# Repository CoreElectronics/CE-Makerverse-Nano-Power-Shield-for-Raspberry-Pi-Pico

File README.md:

# Makerverse™ Nano Power Timer HAT for Raspberry Pi Pico

This is the repo for the Core Electronics [Makerverse Nano Power Timer HAT for Raspberry Pi Pico](https://core-electronics.com.au/catalog/product/view/sku/ce08492).

The PCB layout project requires KiCAD 6.0 or newer to view. The schematic is provided in PDF format in the Documents folder.

## License
This project is open source - please review the LICENSE.md file for further licensing information.

If you have any technical questions, or concerns about licensing, please contact technical support on the [Core Electronics forums](https://forum.core-electronics.com.au/).

*\"PiicoDev\" and the PiicoDev logo are trademarks of Core Electronics Pty Ltd.*

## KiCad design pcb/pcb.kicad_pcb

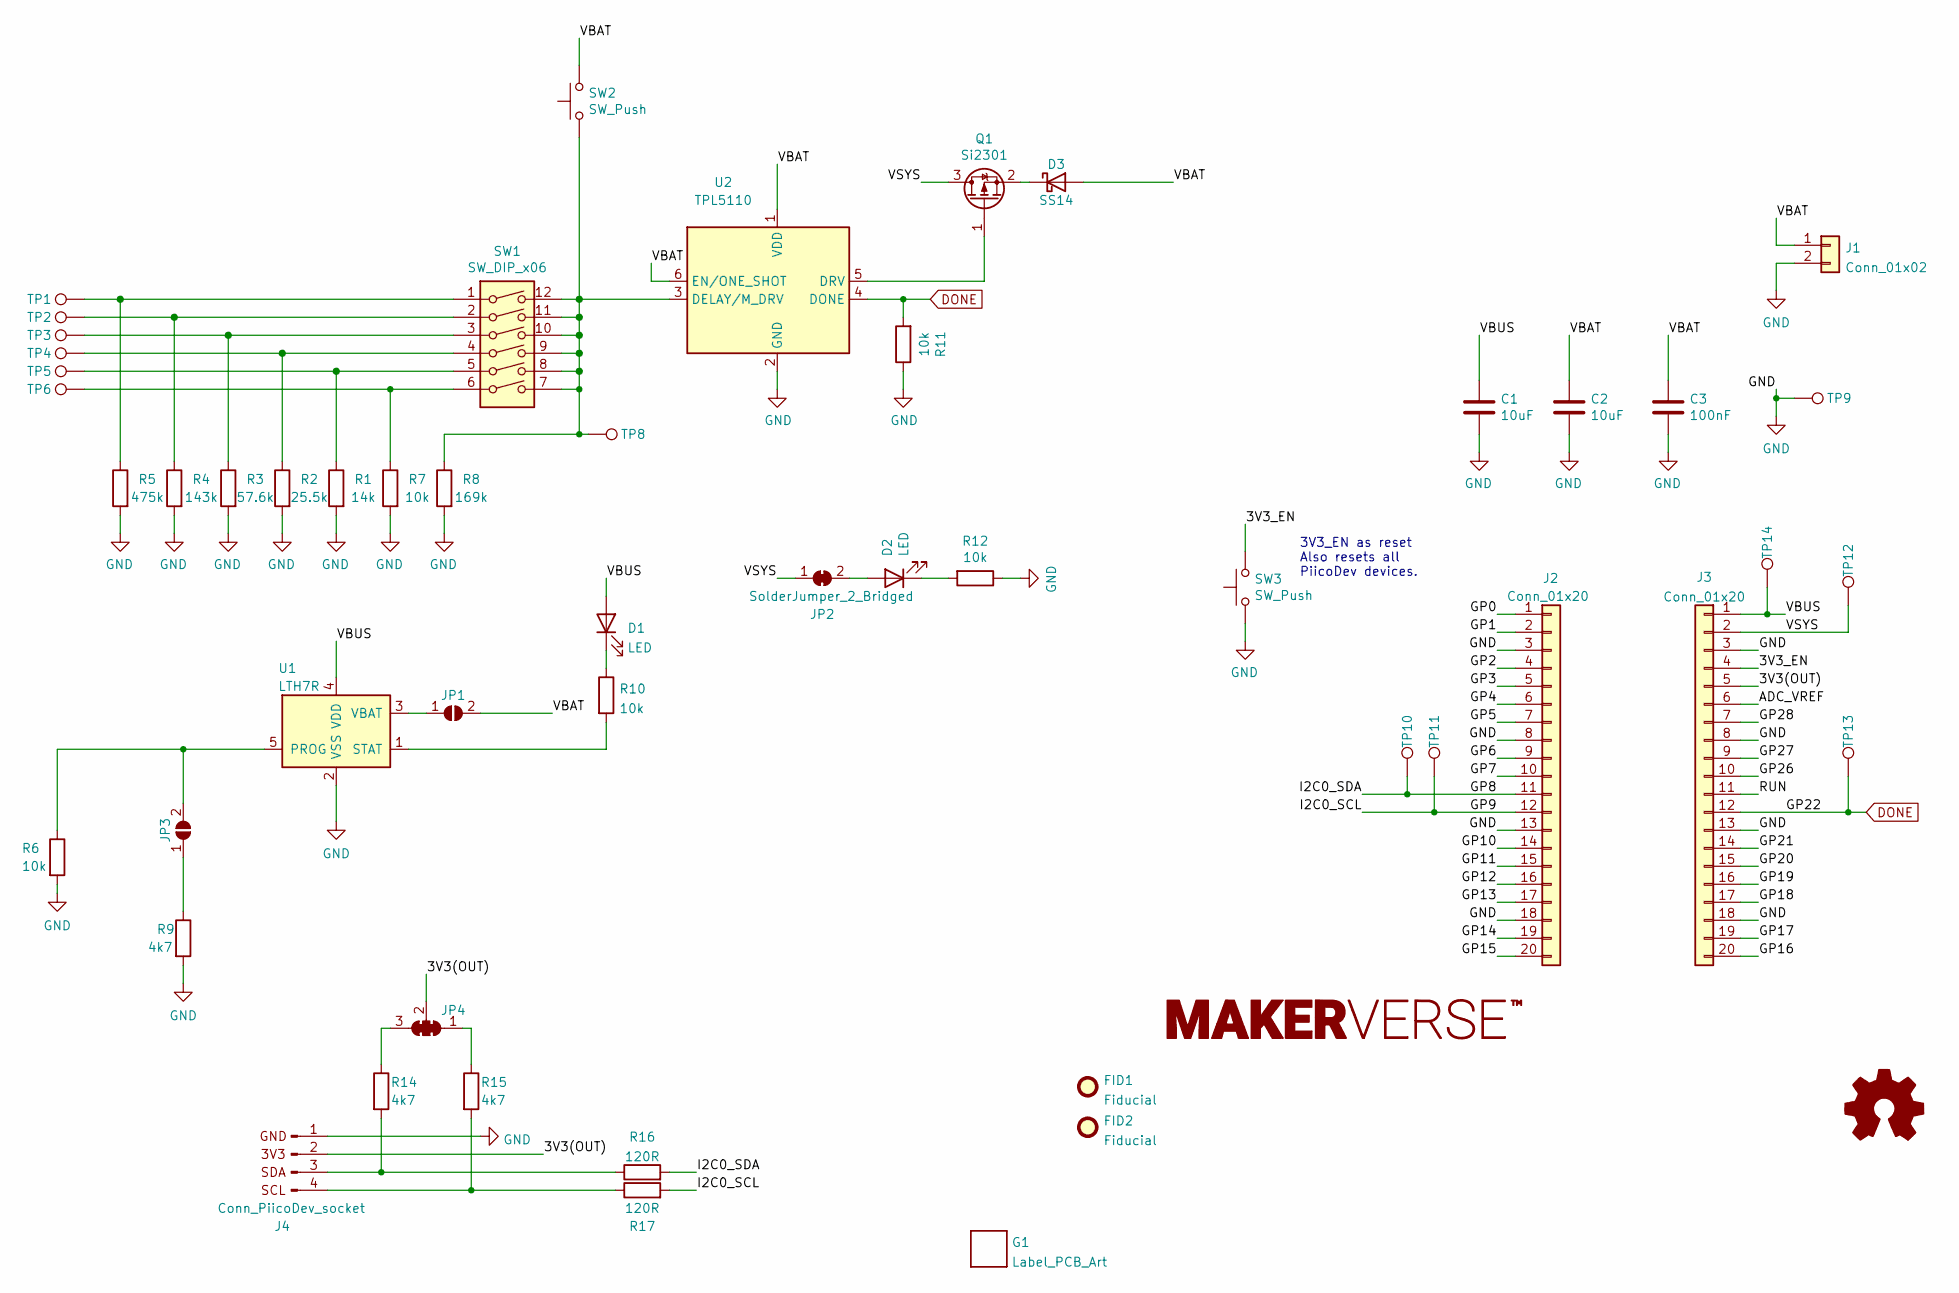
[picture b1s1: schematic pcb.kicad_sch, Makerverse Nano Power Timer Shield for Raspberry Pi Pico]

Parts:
C1, C2: 10uF; C_0603_1608Metric
C3: 100nF; C_0402_1005Metric
D1, D2: LED; LED_0603_1608Metric
D3: SS14; D_SMA
FID1, FID2: Fiducial; Fiducial_1mm_Mask2mm
G1: Label_PCB_Art; CE08492
G2: LOGO_Makerverse; makerverse_logo_short_14.0x2.4mm
J1: Conn_01x02; JST_PH_S2B-PH-SM4-TB_1x02-1MP_P2.00mm_Horizontal
J2, J3: Conn_01x20; PinSocket_1x20_P2.54mm_Vertical-Large-Pads
J4: Conn_PiicoDev_socket; JST_SH_SM04B-SRSS-TB_1x04-1MP_P1.00mm_Horizontal
JP1, JP3: SolderJumper_2_Open; SolderJumper-2_P1.3mm_Open_RoundedPad1.0x1.5mm
JP2: SolderJumper_2_Bridged; SolderJumper-2_P1.3mm_Bridged_RoundedPad1.0x1.5mm
JP4: SolderJumper_3_Bridged123; SolderJumper-3_P1.3mm_Closed_RoundedPad1.0x1.5mm_NumberLabe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
Q1: Si2301; SOT-23
R1: 14k; R_0402_1005Metric
R2: 25.5k; R_0402_1005Metric
R3: 57.6k; R_0402_1005Metric
R4: 143k; R_0402_1005Metric
R5: 475k; R_0402_1005Metric
R6, R7, R10, R11, R12: 10k; R_0402_1005Metric
R8: 169k; R_0402_1005Metric
R9, R14, R15: 4k7; R_0402_1005Metric
R16, R17: 120R; R_0402_1005Metric
SW1: SW_DIP_x06; SW_DIP_SPSTx06_Slide_6.7x16.8mm_W8.61mm_P2.54mm_LowProfile
SW2, SW3: SW_Push; SW_Tactile_5x5
TP1, TP2, TP3, TP4, TP5, TP6, TP8, TP9, TP10, TP11, TP12, TP13, TP14: TestPoint; TestPoint_Pad_D1.5mm
U1: LTH7R; SOT-23-5
U2: TPL5110; SOT-23-6

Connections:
/3V3(OUT): J3.5, J4.2, JP4.2 (C)
/3V3_EN: J3.4, SW3.2
/ADC_VREF: J3.6
/GP0: J2.1
/GP1: J2.2
/GP2: J2.4
/GP3: J2.5
/GP4: J2.6
/GP5: J2.7
/GP6: J2.9
/GP7: J2.10
/GP8: J2.11, R16.2, TP10.1
/GP9: J2.12, R17.2, TP11.1
/GP10: J2.14
/GP11: J2.15
/GP12: J2.16
/GP13: J2.17
/GP14: J2.19
/GP15: J2.20
/GP16: J3.20
/GP17: J3.19
/GP18: J3.17
/GP19: J3.16
/GP20: J3.15
/GP21: J3.14
/GP26: J3.10
/GP27: J3.9
/GP28: J3.7
/RUN: J3.11
/VBAT: C2.1, C3.1, D3.2 (A), J1.1, JP1.2 (B), SW2.2, U2.1 (VDD), U2.6 (EN/ONE_SHOT)
/VBUS: C1.1, D1.2 (A), J3.1, TP14.1, U1.4 (VDD)
/VSYS: J3.2, JP2.1 (A), Q1.3 (D), TP12.1
DONE: J3.12, R11.2, TP13.1, U2.4 (DONE)
GND: C1.2, C2.2, C3.2, J1.2, J2.3, J2.8, J2.13, J2.18, J3.3, J3.8, J3.13, J3.18, J4.1, R1.2, R2.2, R3.2, R4.2, R5.2, R6.2, R7.2, R8.2, R9.2, R11.1, R12.1, SW3.1, TP9.1, U1.2 (VSS), U2.2 (GND)
unnamed: D1.1 (K), R10.1
unnamed: D2.1 (K), R12.2
unnamed: D2.2 (A), JP2.2 (B)
unnamed: D3.1 (K), Q1.2 (S)
unnamed: J4.3, R14.2, R16.1
unnamed: J4.4, R15.2, R17.1
unnamed: JP1.1 (A), U1.3 (VBAT)
unnamed: JP3.1 (A), R9.1
unnamed: JP3.2 (B), R6.1, U1.5 (PROG)
unnamed: JP4.1 (A), R15.1
unnamed: JP4.3 (B), R14.1
unnamed: Q1.1 (G), U2.5 (DRV)
unnamed: R1.1, SW1.5, TP5.1
unnamed: R2.1, SW1.4, TP4.1
unnamed: R3.1, SW1.3, TP3.1
unnamed: R4.1, SW1.2, TP2.1
unnamed: R5.1, SW1.1, TP1.1
unnamed: R7.1, SW1.6, TP6.1
unnamed: R8.1, SW1.7, SW1.8, SW1.9, SW1.10, SW1.11, SW1.12, SW2.1, TP8.1, U2.3 (DELAY/M_DRV)
unnamed: R10.2, U1.1 (STAT)

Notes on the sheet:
3V3_EN as reset Also resets all PiicoDev devices.

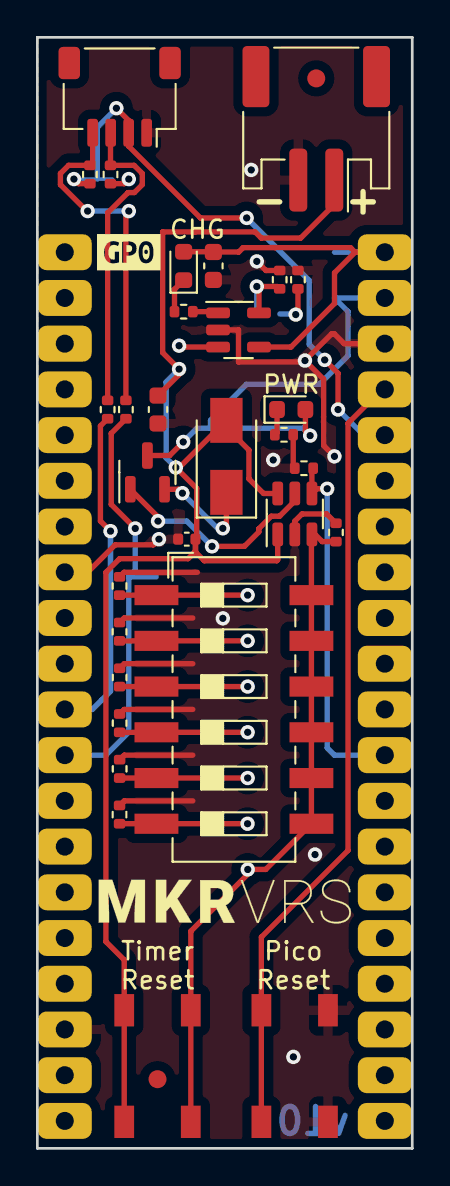
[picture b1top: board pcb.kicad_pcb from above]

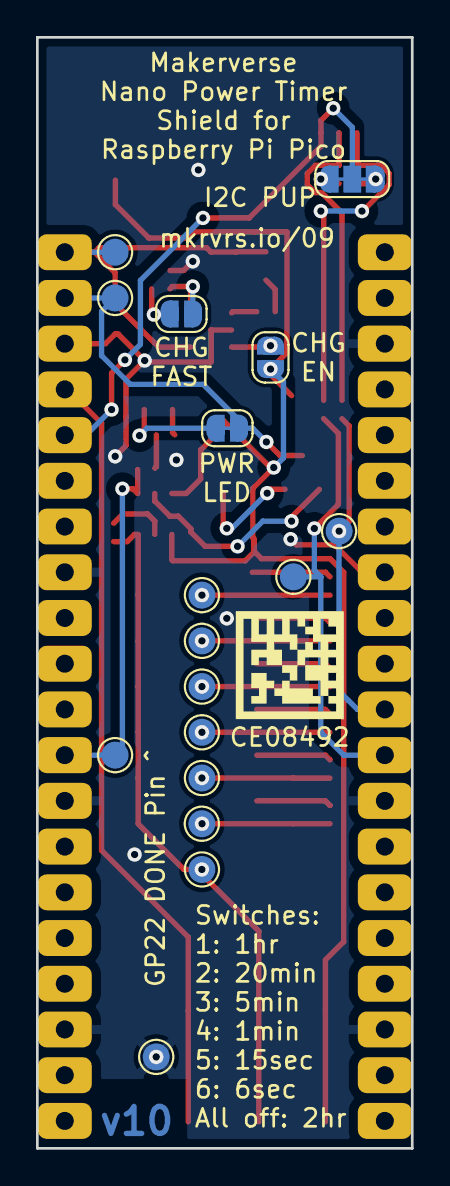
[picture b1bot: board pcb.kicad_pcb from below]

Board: 2 copper layers, 20.8 x 61.7 mm, 54 parts (18 on the bottom side), 29 nets.

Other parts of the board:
kibuzzard-624E6047: G***; kibuzzard-624E6047

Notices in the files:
pcb/pcb.kicad_sch:
License: CCASAv4.0 https://creativecommons.org/licenses/by-sa/4.0
